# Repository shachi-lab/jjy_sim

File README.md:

# 📡 JJY-SIM R4 (with R3 design references)

Build your own JJY time-signal simulator with an ESP32-C3 or ESP8684!  
This compact simulator reproduces the 40 kHz / 60 kHz JJY radio time signal using PWM output,  
based on accurate time obtained from NTP.  
R2, R3 and R4 share an ESP-IDF firmware codebase.  

**R4 is the latest model. The older R3 design files are retained for reference.**

The firmware version is **1.2.0**.

👉 [README 日本語版はこちら](README_ja.md)

---

## R4 / R3 / R2 layout

| Item | R4 (latest model) | R3 (older model, for reference) | R2 (older model) |
|---|---|---|---|
| Exterior | Antenna inside the case | Antenna outside the case | Similar to R3 |
| MCU | ESP32-C3 | ESP8684 (ESP32-C2) | ESP32-C3 |
| Resonance selection | Automatic switching via GPIO3 | On-board switch | Solder jumpers |
| Firmware | Shared source, esp32c3 build | Shared source, esp32c2 build | Shared source, esp32c3 build |
| Hardware design files | Included (r4 / r4.1, r4_ant)| Included for reference (r3)| Not included |

R3 and R4 use PCB antennas. R4 stacks a main PCB and three antenna PCBs inside the case. R3 integrates the main circuitry and antenna on one PCB, with the antenna extending outside the case.

R2 has an exterior similar to R3, but uses an ESP32-C3 and solder jumpers for resonance selection. It can use the C3 build of the shared firmware. R2 hardware design files are not included in this repository.

The shared R2/R3/R4 firmware sources are in `firmware/idf/jjy-sim`.
R4 is identified by the eFuse field `USER_DATA_JJYSIM_HW_GENERATION` set to `4`. An unconfigured ESP32-C3 runs as R2. A self-built R4 requires this identification field to be programmed. eFuse writes are irreversible; verify the board and `main/esp_efuse_custom_table.csv` before programming.

See the [USB flashing instructions (Japanese)](firmware/idf/jjy-sim/README.md).

Board designs are in `hardware/KiCad/r3`, `r4`, `r4.1` and `r4_ant`, with shared libraries in `hardware/KiCad/lib`. Each board has its own `PLOT` directory. Case models are in `hardware/case_3d/r3` and `r4`.

`hardware/KiCad/r4.1` contains an alternative component layout for the R4 PCB. The order of the L/C/R components in the resonant circuit has also been changed to accommodate the new layout.

## 🪛 Features

* Generates **JJY 40 kHz / 60 kHz** signals from time obtained via **NTP**
* Equipped with a **PCB antenna** (inside the case on R4)
* Shows the time and operating status on an **OLED display**
* Configures Wi-Fi and operating settings through a **web browser**
* Supports **Hourly Mode, Night Mode and a screen saver**
* Distributes time to devices on the LAN as an **NTP server**
* Supports firmware updates over Wi-Fi via **OTA updates**

*R4 exterior*  

<br/>

*For reference: the older R3 model below*  

<br/>

---

## 🛠 Build and Flash (ESP-IDF / CLI)

Use **ESP-IDF v5.5.4** and run these commands from `firmware/idf/jjy-sim`. Arduino builds are not supported.

R3 (ESP8684 / ESP32-C2):

```bash
idf.py -B build-c2 -D IDF_TARGET=esp32c2 -D SDKCONFIG=sdkconfig.c2 build
idf.py -B build-c2 -D IDF_TARGET=esp32c2 -D SDKCONFIG=sdkconfig.c2 -p COMx flash monitor
```

R4 (ESP32-C3):

```bash
idf.py -B build -D IDF_TARGET=esp32c3 -D SDKCONFIG=sdkconfig.c3 build
idf.py -B build -D IDF_TARGET=esp32c3 -D SDKCONFIG=sdkconfig.c3 -p COMx flash monitor
```

Replace `COMx` with your serial port. `partitions.csv` defines the OTA partition layout. Migration from the old layout requires USB flashing including the partition table, not just the application image.

### Program the R4 identification eFuse

The ESP32-C3 on a self-built R4 needs the identification value `4`. **Do not run this procedure on R3. eFuse programming is irreversible.**

In an ESP-IDF environment, change to `firmware/idf/jjy-sim` and replace `COMx` with the port of the target R4. These commands use a USB connection.

First, check the current value:

```powershell
espefuse --chip esp32c3 -p COMx --before usb_reset --extend-efuse-table main/esp_efuse_custom_table.csv summary
```

Confirm that `USER_DATA_JJYSIM_HW_GENERATION` is `0` (unprogrammed) before writing `4` with the command below. If it is already `4`, no write is needed. For any other value, do not attempt to overwrite it using this procedure.

```powershell
espefuse --chip esp32c3 -p COMx --before usb_reset --extend-efuse-table main/esp_efuse_custom_table.csv burn_efuse USER_DATA_JJYSIM_HW_GENERATION 4
```

Review the target and changes shown by the tool, then follow its confirmation prompt. After programming, run the `summary` command again and confirm that the value is `4`. Restart the board so that the firmware identifies it as R4.

---
## 🛠 Build and Flash (VSCode / GUI)

You can also develop this project using **VSCode + the ESP-IDF Extension**.

### ■ Recommended Extension

* ESP-IDF Extension (Espressif)

By installing the extension in VSCode, you can perform the following from the GUI:

* Build
* Flash
* Serial monitor

### ■ Setup

Set up your environment according to the ESP-IDF Extension instructions.

Once the extension is installed, you can run actions such as:

* `Build`
* `Flash`
* `Monitor`

with a single click.

### ■ Workspace

When opening the project in VSCode,
open **`JJY-SIM.code-workspace`** in the source-code folder
then select your local ESP-IDF 5.5.4 installation and either `C3 (R2 / R4)` or `C2 (R3)` configuration.

---

## ⚙️ Usage

Refer to the model-specific manuals on the [JJY-SIM support page](https://blog.shachi-lab.com/support/) for settings, screens and controls.
R4 switches its resonance circuit automatically with the BAND setting. On R3, also set the on-board switch to match the selected BAND.

---
## 🔌 Pin Assignment (Main Signals)

| Function       | GPIO | Notes                                                        |
| -------------- | ---- | ------------------------------------------------------------ |
| JJY PWM output | 10,4 | Modulated output signals, inverted A/B pair for the H-bridge |
| R4 BAND selection | 3 | R4 only; resonance circuit switching |
| CONFIG switch  | 9    | Used for Wi-Fi setup (**shared with BOOT pin**)              |
| ACT LED        | 5    | Activity LED                                                 |
| IND LED        | 0    | Status indicator LED (can be shared)                         |
| OLED Reset     | 2    | OLED module reset                                            |
| OLED SDA       | 7    | OLED I2C data                                                |
| OLED SCL       | 6    | OLED I2C clock                                               |

---

## 🧾 File Structure

### 💻 Firmware

* The firmware source code is located in the **`firmware/idf`** folder.
* This firmware uses a rebuilt library, ported as an IDF component, based on the Arduino OLED driver library used in R2.  
This component is publicly available on GitHub.  
👉 [SSD1306 OLED display driver](https://github.com/Shachi-lab/oled_display)
* `storage_key.h` contains placeholder values and can be used as-is.  
  For better security, you may want to replace them with your own values before building.

### 🧰 Hardware

* The hardware design files are located in the **`hardware`** folder.
* The schematic and PCB design data are in **`hardware/KiCad`**.

  * Saved with **KiCad 10** (R4 design files require KiCad 10 or later)
  * **Gerber data** is included in **`hardware/KiCad/<revision>/PLOT`**, so the board can be fabricated as-is
* The 3D case data is in **`hardware/case_3d`**.

---

## 🔧 DIY Assembly

### R4 antenna

Building an R4 requires **stacking three antenna PCBs**. The antenna stack and main PCB fit inside the case.

PCB thickness: **1.6 mm for the main PCB and 0.8 mm for each antenna PCB**.

### OLED supports (R3 / R4)

Both R3 and R4 PCBs include tab-shaped sections for the OLED supports. **Break these sections off during assembly and use them as supports for the OLED.**

### Case screws

Use **hex M2 × 5 mm self-tapping screws** to fasten the case.

---

## 📸 Appearance / Assembly Examples

The photos below show the R4 board and case.  
The design uses a black PCB and a black case so that only the display appears to float visually.

<br/>

### R3 (for reference)

The photos below show the R3 board and case.  

<br/>

---

## ⚠️ Caution

The R4 antenna section becomes slightly warm during operation.

This device may radiate farther than expected.  
Please make sure to comply with applicable radio regulations when experimenting with it.

---

## 🔗 Support / Documentation  

For the latest information, setup guide, and detailed usage notes, please see the support page.  
👉 [JJY-SIM Support Page](https://blog.shachi-lab.com/support/)  
>Note: The support page is currently available in Japanese only.

---
## 📝 Attribution

JJY-SIM is released under the MIT License.  
You are free to use, modify, and build upon this project.  

When selling, distributing, or publicly releasing something based on JJY-SIM, please include attribution to **Shachi-lab / JJY-SIM** somewhere visible, such as the product page, documentation, README, package, or other accompanying materials.

Example:

* Designed by Shachi-lab
* Based on JJY-SIM by Shachi-lab
* Inspired by JJY-SIM by Shachi-lab

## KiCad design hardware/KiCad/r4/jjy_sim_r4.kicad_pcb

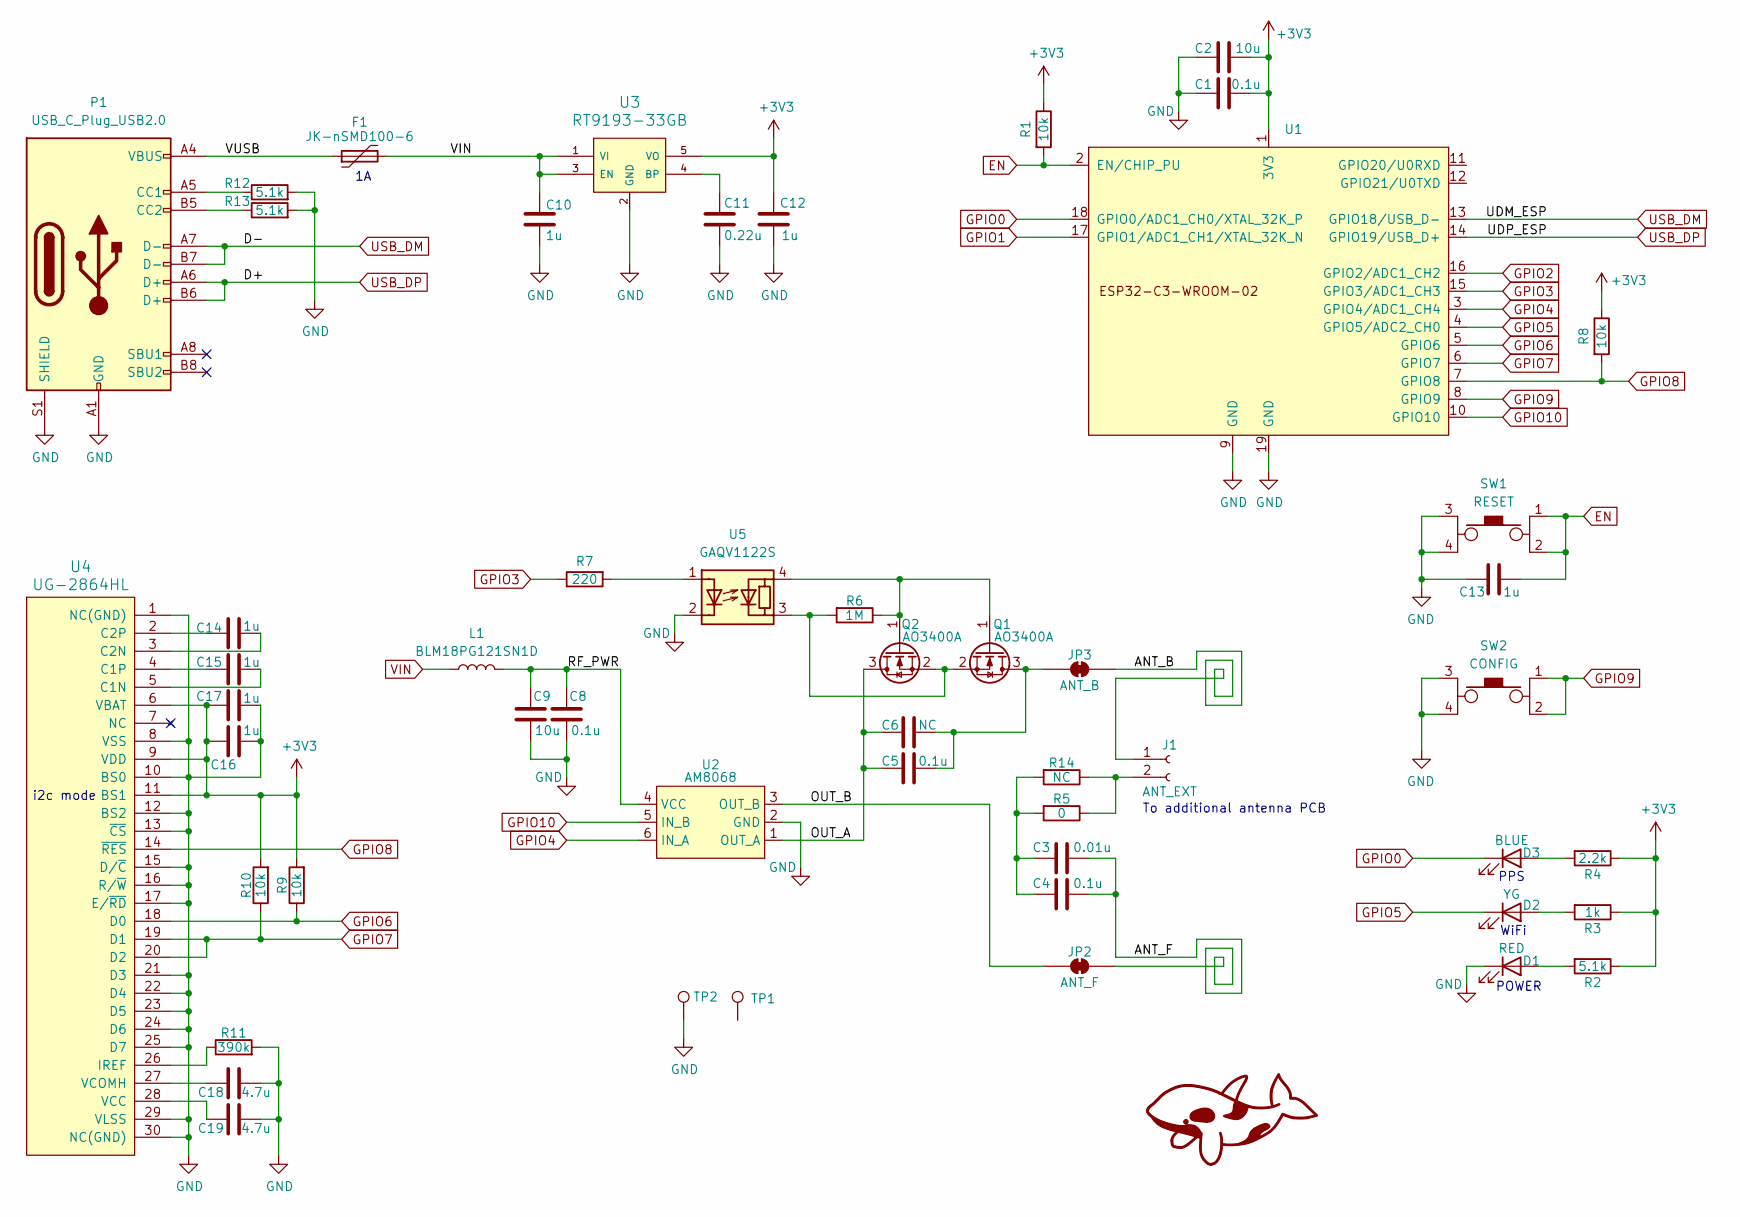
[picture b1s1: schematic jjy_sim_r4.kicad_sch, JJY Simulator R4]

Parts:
C1, C4, C5, C8: 0.1u; C_0603_1608Metric
C2, C9: 10u; C_0805_2012Metric
C3: 0.01u; C_0603_1608Metric
C6: NC; C_0603_1608Metric
C10, C12, C13, C14, C15, C16, C17: 1u; C_0603_1608Metric
C11: 0.22u; C_0603_1608Metric
C18, C19: 4.7u; C_0603_1608Metric
D1: RED; LED_0603_1608Metric
D2: YG; LED_0603_1608Metric
D3: BLUE; LED_0603_1608Metric
F1: JK-nSMD100-6; Fuse_1206_3216Metric
J1: ANT_EXT; PinHeader_1x02_P2.00mm_Vertical
JP2: ANT_F; SolderJumper-2_P1.3mm_Bridged2Bar_RoundedPad1.0x1.5mm
JP3: ANT_B; SolderJumper-2_P1.3mm_Bridged2Bar_RoundedPad1.0x1.5mm
L1: BLM18PG121SN1D; L_0603_1608Metric
P1: USB_C_Plug_USB2.0; 5077CR-16SMC2-BK-TR
Q1, Q2: AO3400A; SOT-23
R1, R8, R9, R10: 10k; R_0603_1608Metric
R2, R12, R13: 5.1k; R_0603_1608Metric
R3: 1k; R_0603_1608Metric
R4: 2.2k; R_0603_1608Metric
R5: 0; R_0603_1608Metric
R6: 1M; R_0603_1608Metric
R7: 220; R_0603_1608Metric
R11: 390k; R_0603_1608Metric
R14: NC; R_2512_6332Metric
SW1: RESET; SKRPACE010
SW2: CONFIG; SKRPACE010
TP1, TP2: ANT_EX; TestPoint_THTPad_D1.0mm_Drill0.5mm
U1: ESP32-C3-WROOM-02
U2: AM8068; SOT-23-6
U3: RT9193-33GB; SOT-23-5
U4: UG-2864HL; UG-2864-FPC (Reverse)
U5: GAQV1122S; SOP-4_3.8x4.1mm_P2.54mm

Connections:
+3V3: C1.2, C2.2, C12.1, C16.1, C17.1, R1.1, R2.1, R3.1, R4.1, R8.1, R9.2, R10.2, U1.1 (3V3), U3.5 (VO), U4.6 (VBAT), U4.9 (VDD), U4.11 (BS1)
/ANT_B: J1.1, JP3.2 (B)
/ANT_F: C3.2, C4.2, JP2.2 (B)
/OUT_A: C5.1, C6.1, Q2.3 (D), U2.1 (OUT_A)
/OUT_B: JP2.1 (A), U2.3 (OUT_B)
/RF_PWR: C8.1, C9.1, L1.2, U2.4 (VCC)
/VUSB: F1.1, P1.A4 (VBUS), P1.A9 (VBUS), P1.B4 (VBUS), P1.B9 (VBUS)
EN: C13.2, R1.2, SW1.1, SW1.2, U1.2 (EN/CHIP_PU)
GND: C1.1, C2.1, C8.2, C9.2, C10.2, C11.2, C12.2, C13.1, C16.2, C17.2, C18.2, C19.2, D1.1 (K), P1.A1 (GND), P1.A12 (GND), P1.B1 (GND), P1.B12 (GND), P1.S1 (SHIELD), R11.2, R12.2, R13.2, SW1.3, SW1.4, SW2.3, SW2.4, TP2.1 (1_1), U1.9 (GND), U1.19 (GND), U2.2 (GND), U3.2 (GND), U4.1 (NC(GND)), U4.8 (VSS), U4.10 (BS0), U4.12 (BS2), U4.13 (~CS), U4.15 (D/~C), U4.16 (R/~W), U4.17 (E/~RD), U4.21 (D3), U4.22 (D4), U4.23 (D5), U4.24 (D6), U4.25 (D7), U4.29 (VLSS), U4.30 (NC(GND)), U5.2 (K)
GPIO0: D3.1 (K), U1.18 (GPIO0/ADC1_CH0/XTAL_32K_P)
GPIO1: U1.17 (GPIO1/ADC1_CH1/XTAL_32K_N)
GPIO2: U1.16 (GPIO2/ADC1_CH2)
GPIO3: R7.1, U1.15 (GPIO3/ADC1_CH3)
GPIO4: U1.3 (GPIO4/ADC1_CH4), U2.6 (IN_A)
GPIO5: D2.1 (K), U1.4 (GPIO5/ADC2_CH0)
GPIO6: R9.1, U1.5 (GPIO6), U4.18 (D0)
GPIO7: R10.1, U1.6 (GPIO7), U4.19 (D1), U4.20 (D2)
GPIO8: R8.2, U1.7 (GPIO8), U4.14 (~RES)
GPIO9: SW2.1, SW2.2, U1.8 (GPIO9)
GPIO10: U1.10 (GPIO10), U2.5 (IN_B)
unnamed: C3.1, C4.1, R5.2, R14.2
unnamed: D1.2 (A), R2.2
unnamed: D2.2 (A), R3.2
unnamed: D3.2 (A), R4.2
unnamed: J1.2, R5.1, R14.1
unnamed: C5.2, C6.2, JP3.1 (A), Q1.3 (D)
unnamed: P1.A5 (CC1), R12.1
unnamed: P1.B5 (CC2), R13.1
unnamed: Q1.1 (G), Q2.1 (G), R6.1, U5.4 (R)
unnamed: Q1.2 (S), Q2.2 (S), R6.2, U5.3 (R)
unnamed: C11.1, U3.4 (BP)
unnamed: C15.2, U4.5 (C1N)
unnamed: C15.1, U4.4 (C1P)
unnamed: C14.2, U4.3 (C2N)
unnamed: C14.1, U4.2 (C2P)
unnamed: R11.1, U4.26 (IREF)
unnamed: C19.1, U4.28 (VCC)
unnamed: C18.1, U4.27 (VCOMH)
unnamed: R7.2, U5.1 (A)
USB_DM: P1.A7 (D-), P1.B7 (D-), U1.13 (GPIO18/USB_D-)
USB_DP: P1.A6 (D+), P1.B6 (D+), U1.14 (GPIO19/USB_D+)
VIN: C10.1, F1.2, L1.1, U3.1 (VI), U3.3 (EN)

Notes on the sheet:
To additional antenna PCB
PPS
i2c mode
WiFi
POWER

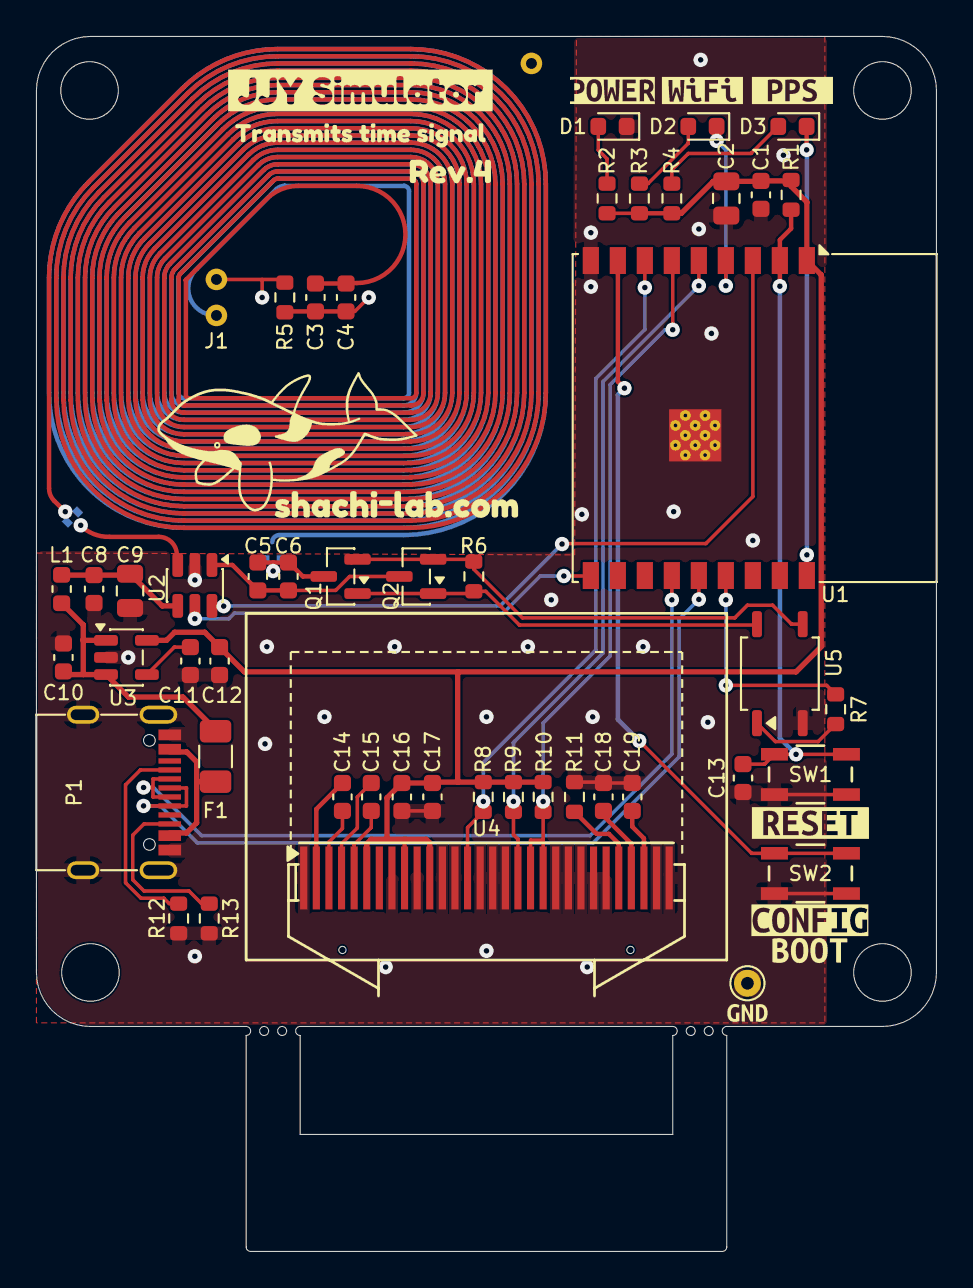
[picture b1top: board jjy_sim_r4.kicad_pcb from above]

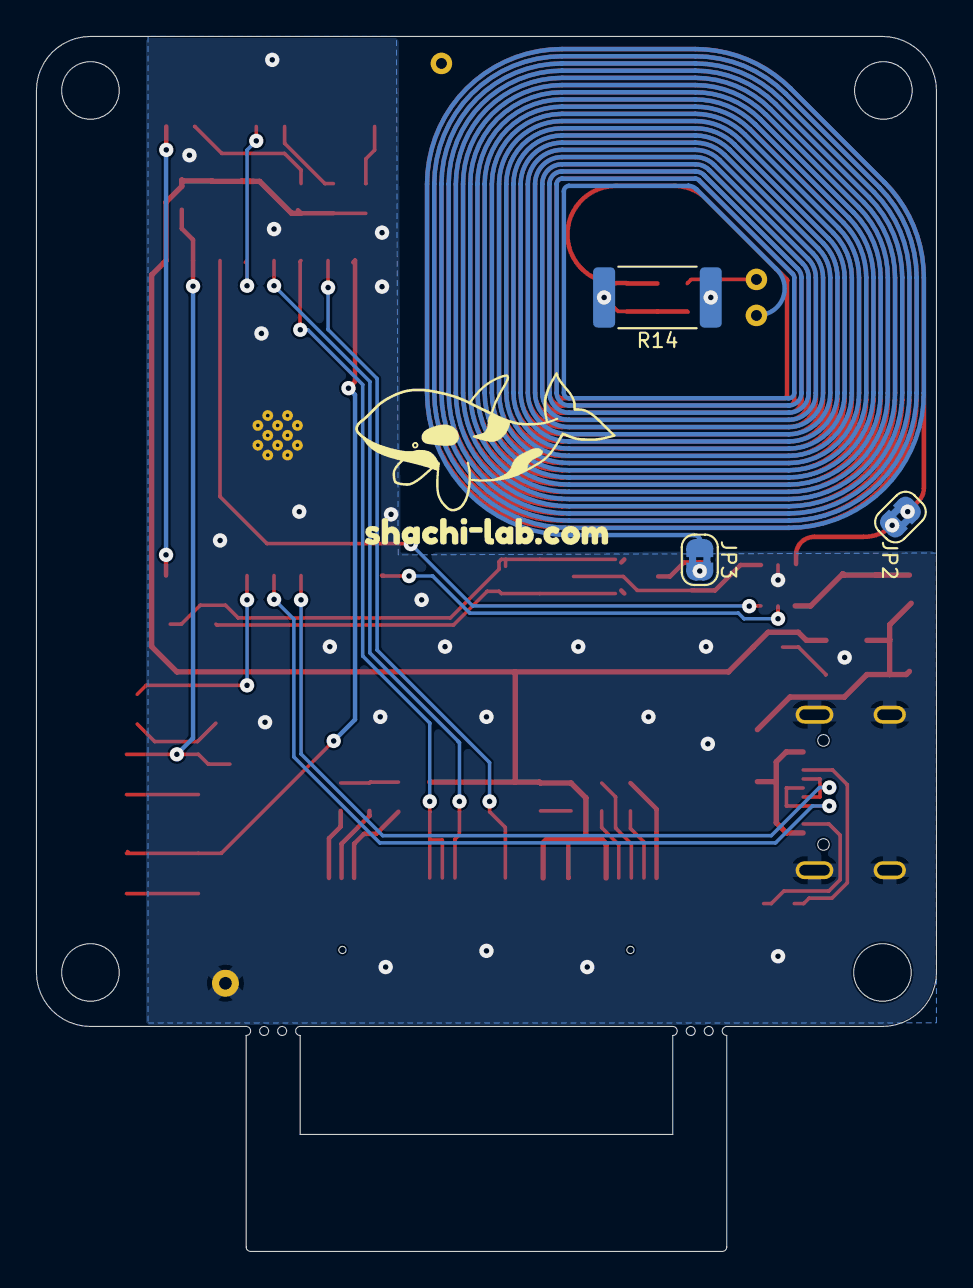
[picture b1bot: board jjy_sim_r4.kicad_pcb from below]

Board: 2 copper layers, 50.0 x 67.5 mm, 68 parts (4 on the bottom side), 40 nets.

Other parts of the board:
1, 2, 3, 4: (no value)
kibuzzard-1: G***; kibuzzard-68D3A9C1
kibuzzard-2: G***; kibuzzard-6A7AED3A
kibuzzard-3: G***; kibuzzard-6A7AED45
kibuzzard-4: G***; kibuzzard-6A7AED2D
kibuzzard-5: G***; kibuzzard-68D3A910
kibuzzard-6: G***; kibuzzard-6A7AE0A2
kibuzzard-7, kibuzzard-12: G***; kibuzzard-68D2B4BB
kibuzzard-8: G***; kibuzzard-665B3587
kibuzzard-9: G***; kibuzzard-665B357F
kibuzzard-10: G***; kibuzzard-669B16B9
kibuzzard-11: G***; kibuzzard-665B35AE

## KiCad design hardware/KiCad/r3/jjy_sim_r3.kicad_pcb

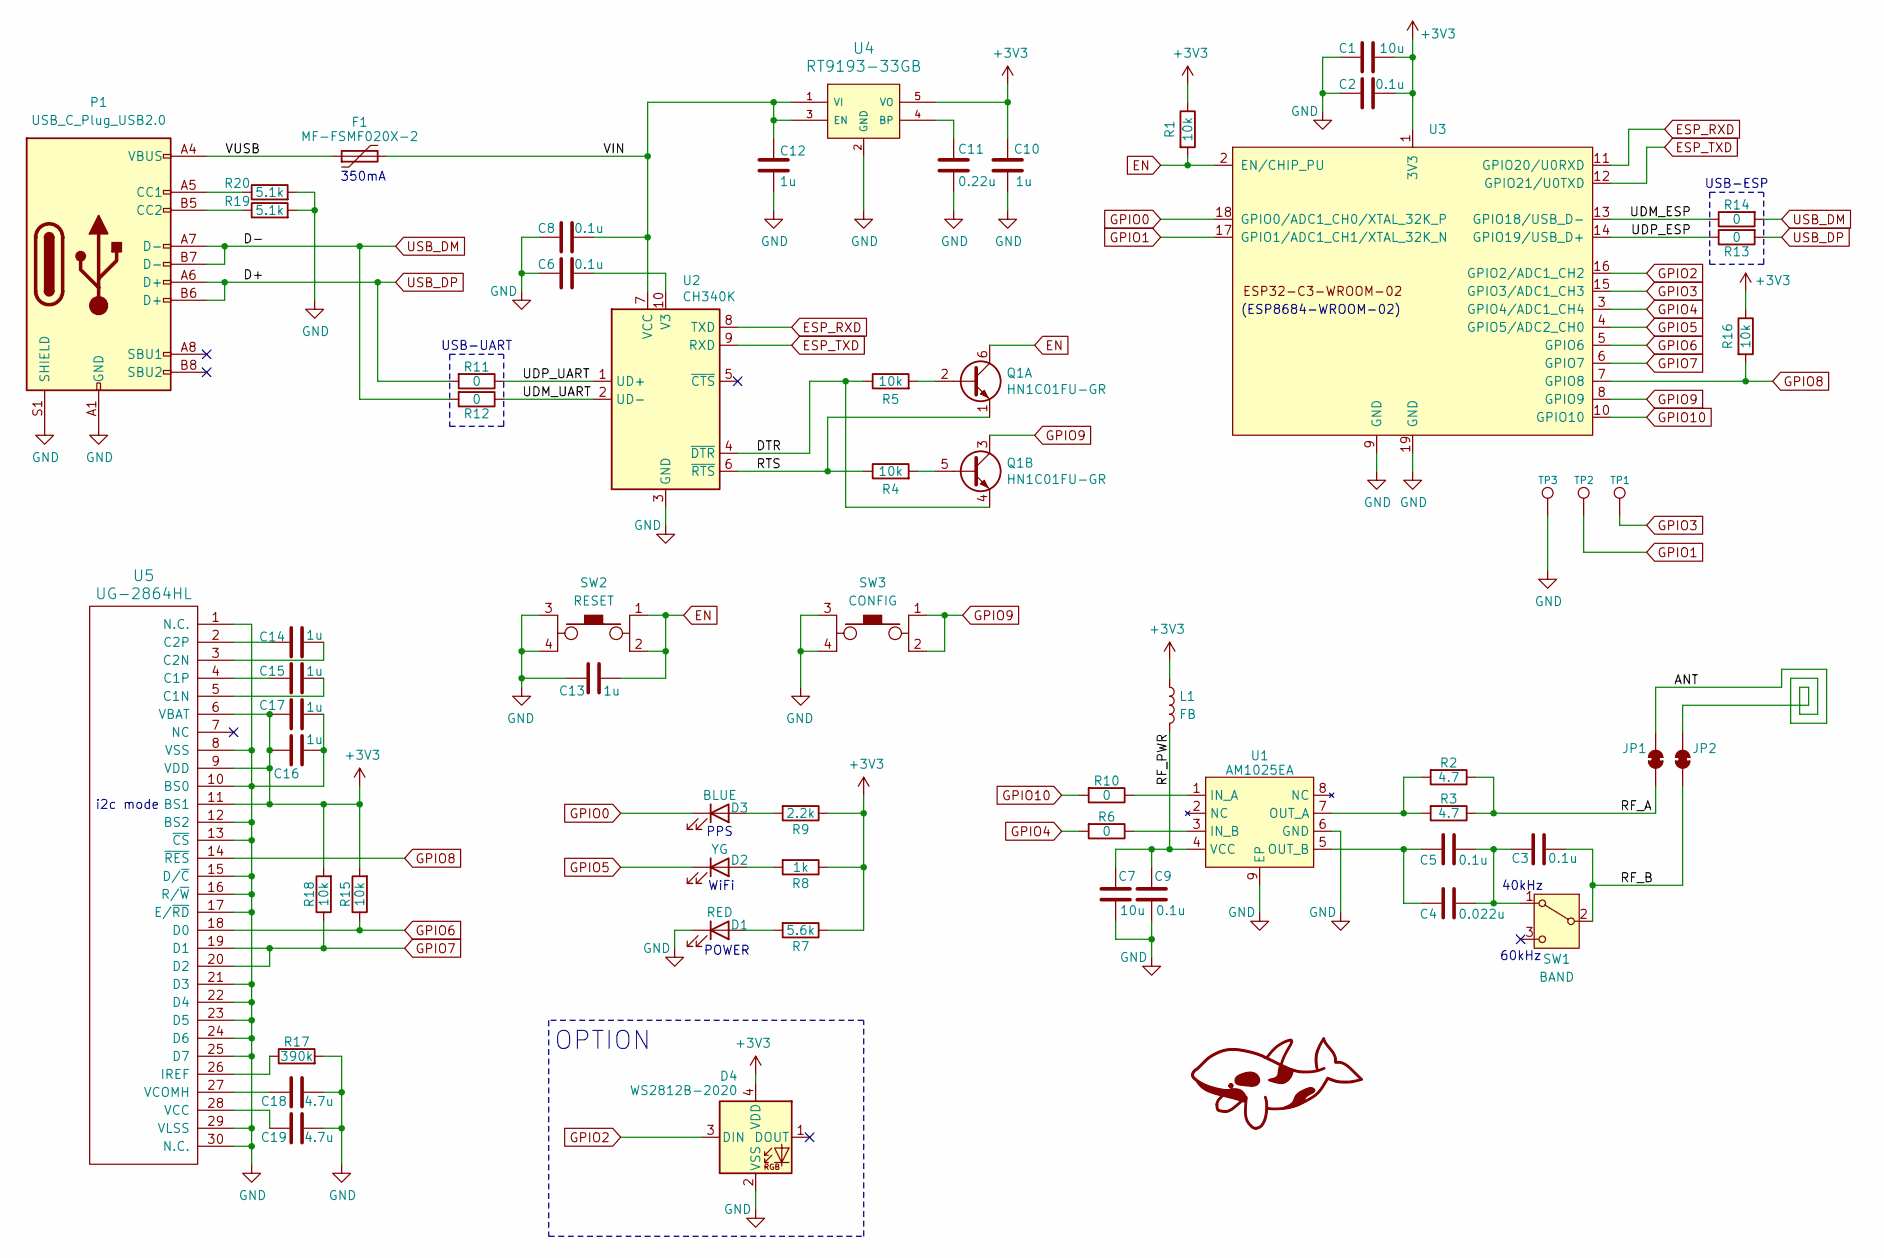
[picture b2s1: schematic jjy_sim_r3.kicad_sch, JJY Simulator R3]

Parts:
C1, C7: 10u; C_0805_2012Metric
C2, C3, C5, C6, C8, C9: 0.1u; C_0603_1608Metric
C4: 0.022u; C_0603_1608Metric
C10, C12, C13, C14, C15, C16, C17: 1u; C_0603_1608Metric
C11: 0.22u; C_0603_1608Metric
C18, C19: 4.7u; C_0603_1608Metric
D1: RED; LED_0603_1608Metric
D2: YG; LED_0603_1608Metric
D3: BLUE; LED_0603_1608Metric
D4: WS2812B-2020; LED_WS2812B-2020_PLCC4_2.0x2.0mm
F1: MF-FSMF020X-2; Fuse_1206_3216Metric_Pad1.42x1.75mm_HandSolder
JP1: ANT-A; Jumper-2_TH_3.81mm
JP2: GND; Jumper-2_TH_3.81mm
L1: FB; L_0603_1608Metric
P1: USB_C_Plug_USB2.0; 5077CR-16SMC2-BK-TR_Ext
Q1: HN1C01FU-GR; 2-2J1A
R1, R4, R5, R15, R16, R18: 10k; R_0603_1608Metric
R2, R3: 4.7; R_0603_1608Metric
R6, R10, R11, R12, R13, R14: 0; R_0603_1608Metric
R7: 5.6k; R_0603_1608Metric
R8: 1k; R_0603_1608Metric
R9: 2.2k; R_0603_1608Metric
R17: 390k; R_0603_1608Metric
R19, R20: 5.1k; R_0603_1608Metric
SW1: BAND; MSK-12C02
SW2: RESET; SKRPACE010
SW3: CONFIG; SKRPACE010
TP1, TP2, TP3: TP; TestPoint_THTPad_D1.5mm_Drill0.7mm
U1: AM1025EA; eSOP-8_3.9x5.05mm_EP_3.1x2.2mm_P1.27mm
U2: CH340K; SSOP-10-1EP_3.9x4.9mm_P1mm_EP2.1x3.3mm
U3: ESP32-C3-WROOM-02; ESP32-C3-WROOM-02,ESP8684-WROOM-2C
U4: RT9193-33GB; SOT-23-5
U5: UG-2864HL; UG-2864-FPC (Reverse)

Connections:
+3V3: C1.2, C2.2, C10.1, C16.1, C17.1, D4.4 (VDD), L1.1, R1.1, R7.1, R8.1, R9.1, R15.2, R16.1, R18.2, U3.1 (3V3), U4.5 (VO), U5.6 (VBAT), U5.9 (VDD), U5.11 (BS1)
/ANT: JP1.2 (B), JP2.2 (B)
/DTR: Q1.4 (E2), R5.1, U2.4 (~DTR)
/RF_A: JP1.1 (A), R2.1, R3.1
/RF_B: C3.2, JP2.1 (A), SW1.2 (B)
/RF_PWR: C7.1, C9.1, L1.2, U1.4 (VCC)
/RTS: Q1.1 (E1), R4.1, U2.6 (~RTS)
/UDM_ESP: R14.1, U3.13 (GPIO18/USB_D-)
/UDM_UART: R12.1, U2.2 (UD-)
/UDP_ESP: R13.1, U3.14 (GPIO19/USB_D+)
/UDP_UART: R11.1, U2.1 (UD+)
/VIN: C8.2, C12.1, F1.2, U2.7 (VCC), U4.1 (VI), U4.3 (EN)
/VUSB: F1.1, P1.A4 (VBUS), P1.A9 (VBUS), P1.B4 (VBUS), P1.B9 (VBUS)
EN: C13.2, Q1.6 (C1), R1.2, SW2.1, SW2.2, U3.2 (EN/CHIP_PU)
ESP_RXD: U2.8 (TXD), U3.11 (GPIO20/U0RXD)
ESP_TXD: U2.9 (RXD), U3.12 (GPIO21/U0TXD)
GND: C1.1, C2.1, C6.1, C7.2, C8.1, C9.2, C10.2, C11.2, C12.2, C13.1, C16.2, C17.2, C18.2, C19.2, D1.1 (K), D4.2 (VSS), P1.A1 (GND), P1.A12 (GND), P1.B1 (GND), P1.B12 (GND), P1.S1 (SHIELD), R17.2, R19.2, R20.2, SW2.3, SW2.4, SW3.3, SW3.4, TP3.1 (1_1), U1.6 (GND), U1.9 (EP), U2.3 (GND), U2.11 (GND), U3.9 (GND), U3.19 (GND), U4.2 (GND), U5.1 (NC(GND)), U5.8 (VSS), U5.10 (BS0), U5.12 (BS2), U5.13 (~CS), U5.15 (D/~C), U5.16 (R/~W), U5.17 (E/~RD), U5.21 (D3), U5.22 (D4), U5.23 (D5), U5.24 (D6), U5.25 (D7), U5.29 (VLSS), U5.30 (NC(GND))
GPIO0: D3.1 (K), U3.18 (GPIO0/ADC1_CH0/XTAL_32K_P)
GPIO1: TP2.1 (1_1), U3.17 (GPIO1/ADC1_CH1/XTAL_32K_N)
GPIO2: D4.3 (DIN), U3.16 (GPIO2/ADC1_CH2)
GPIO3: TP1.1 (1_1), U3.15 (GPIO3/ADC1_CH3)
GPIO4: R6.2, U3.3 (GPIO4/ADC1_CH4)
GPIO5: D2.1 (K), U3.4 (GPIO5/ADC2_CH0)
GPIO6: R15.1, U3.5 (GPIO6), U5.18 (D0)
GPIO7: R18.1, U3.6 (GPIO7), U5.19 (D1), U5.20 (D2)
GPIO8: R16.2, U3.7 (GPIO8), U5.14 (~RES)
GPIO9: Q1.3 (C2), SW3.1, SW3.2, U3.8 (GPIO9)
GPIO10: R10.2, U3.10 (GPIO10)
unnamed: D1.2 (A), R7.2
unnamed: D2.2 (A), R8.2
unnamed: D3.2 (A), R9.2
unnamed: P1.A5 (CC1), R20.1
unnamed: P1.B5 (CC2), R19.1
unnamed: Q1.2 (B1), R5.2
unnamed: Q1.5 (B2), R4.2
unnamed: C3.1, C4.2, C5.2, SW1.1 (A)
unnamed: R10.1, U1.1 (IN_A)
unnamed: R6.1, U1.3 (IN_B)
unnamed: R2.2, R3.2, U1.7 (OUT_A)
unnamed: C4.1, C5.1, U1.5 (OUT_B)
unnamed: C11.1, U4.4 (BP)
unnamed: C15.2, U5.5 (C1N)
unnamed: C15.1, U5.4 (C1P)
unnamed: C14.2, U5.3 (C2N)
unnamed: C14.1, U5.2 (C2P)
unnamed: R17.1, U5.26 (IREF)
unnamed: C19.1, U5.28 (VCC)
unnamed: C18.1, U5.27 (VCOMH)
unnamed: C6.2, U2.10 (V3)
USB_DM: P1.A7 (D-), P1.B7 (D-), R12.2, R14.2
USB_DP: P1.A6 (D+), P1.B6 (D+), R11.2, R13.2

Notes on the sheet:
USB-UART
PPS
OPTION
350mA
i2c mode
60kHz
USB-ESP
WiFi
40kHz
POWER
(ESP8684-WROOM-02)

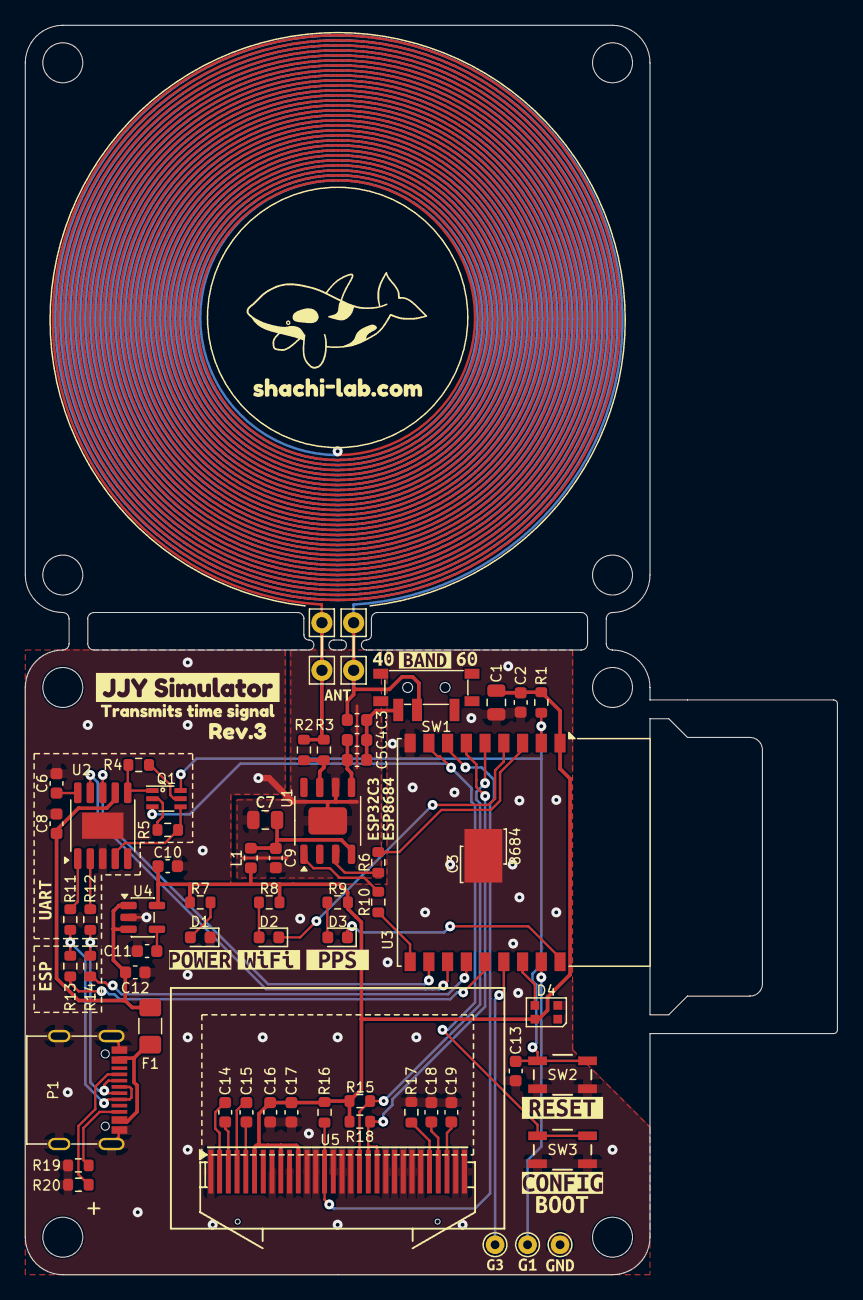
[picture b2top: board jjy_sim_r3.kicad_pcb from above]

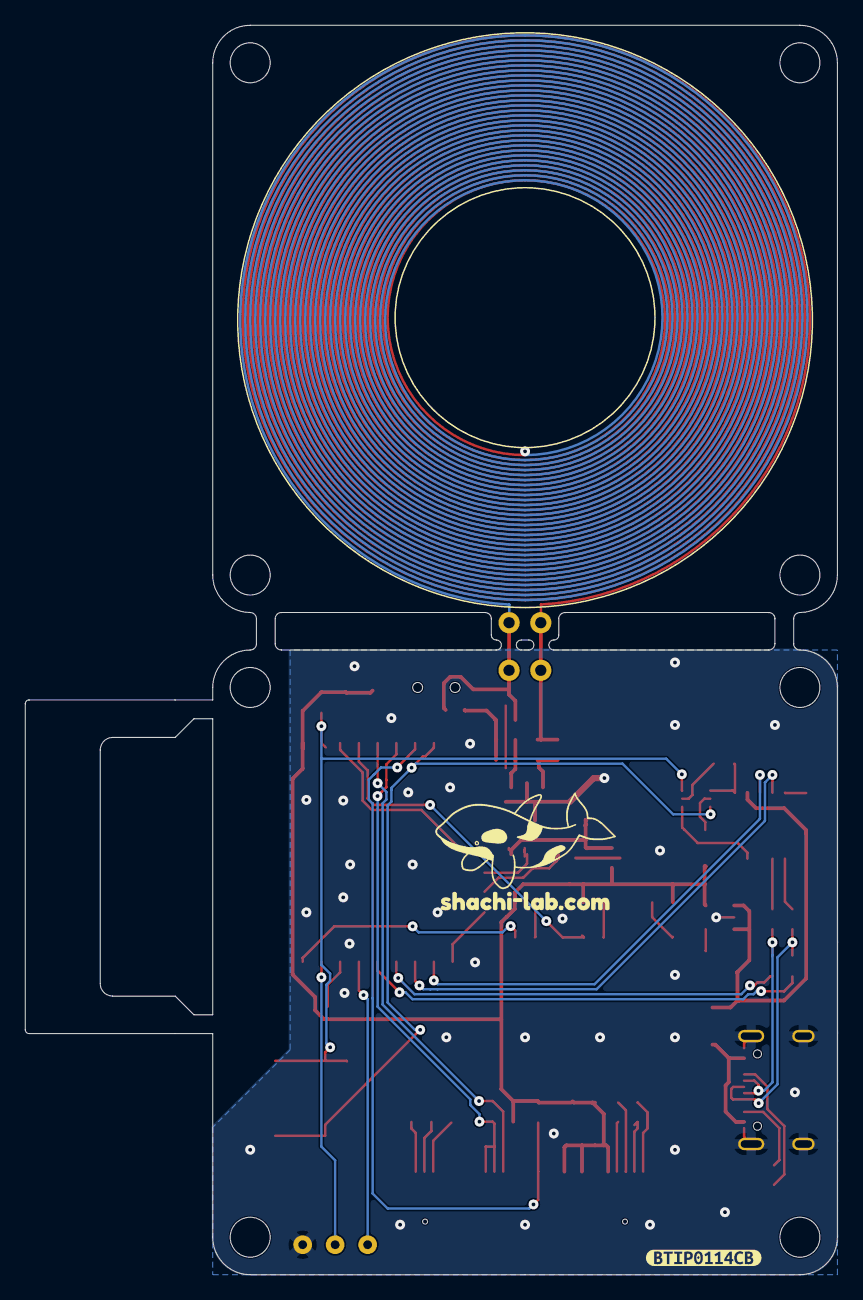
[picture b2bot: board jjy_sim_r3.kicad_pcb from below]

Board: 2 copper layers, 65.0 x 100.0 mm, 90 parts (2 on the bottom side), 51 nets.

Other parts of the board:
1, 2, 3, 4, 5, 6, 7, 8: (no value)
kibuzzard-1, kibuzzard-28: G***; kibuzzard-68D2B4BB
kibuzzard-2: G***; kibuzzard-6982098F
kibuzzard-3: G***; kibuzzard-69820977
kibuzzard-4: G***; kibuzzard-69820ADF
kibuzzard-5: G***; kibuzzard-68D3A9C1
kibuzzard-6: G***; kibuzzard-6646C6AC
kibuzzard-6A179A92: G***; kibuzzard-6A179A92
kibuzzard-7: G***; kibuzzard-68D3A910
kibuzzard-8: G***; kibuzzard-69816480
kibuzzard-9: G***; kibuzzard-69867CAB
kibuzzard-10: G***; kibuzzard-698209E3
kibuzzard-11: G***; kibuzzard-669B6BC9
kibuzzard-12: G***; kibuzzard-669B6DC4
kibuzzard-13: G***; kibuzzard-68E061D7
kibuzzard-14: G***; kibuzzard-69965DBC
kibuzzard-15: G***; kibuzzard-665B3587
kibuzzard-16: G***; kibuzzard-665B357F
kibuzzard-17: G***; kibuzzard-669B16B9
kibuzzard-18: G***; kibuzzard-665A8DD6
kibuzzard-19: G***; kibuzzard-669B4532
kibuzzard-20: G***; kibuzzard-665B35AE
